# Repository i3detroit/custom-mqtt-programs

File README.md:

# I3Detroit custom esp IoT programs
This is where all the non-sonoff stuff that is simple lives

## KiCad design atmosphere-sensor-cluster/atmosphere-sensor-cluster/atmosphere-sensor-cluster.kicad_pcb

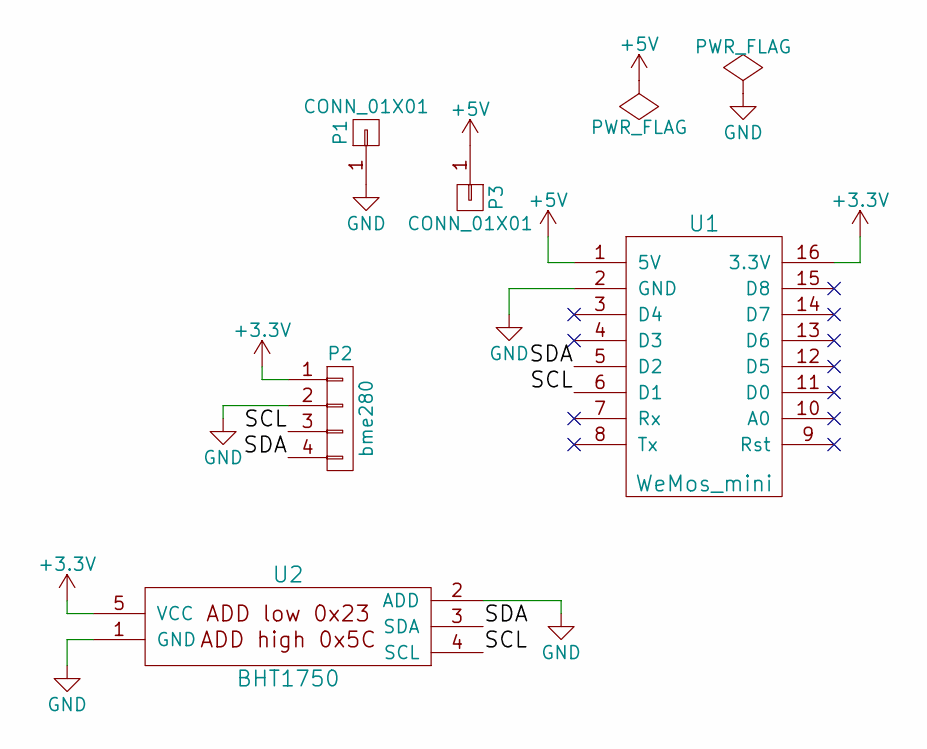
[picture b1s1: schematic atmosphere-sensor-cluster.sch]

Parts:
P1, P3: CONN_01X01; Pin_Header_Straight_1x01
P2: bme280; Pin_Header_Straight_1x04
U1: WeMos_mini; D1_mini_board
U2: BHT1750

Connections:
+3V3: P2.1, U1.16 (3.3V), U2.5 (VCC)
+5V: P3.1, U1.1 (5V)
/SCL: P2.3, U1.6 (D1), U2.4 (SCL)
/SDA: P2.4, U1.5 (D2), U2.3 (SDA)
GND: P1.1, P2.2, U1.2 (GND), U2.1 (GND), U2.2 (ADD)

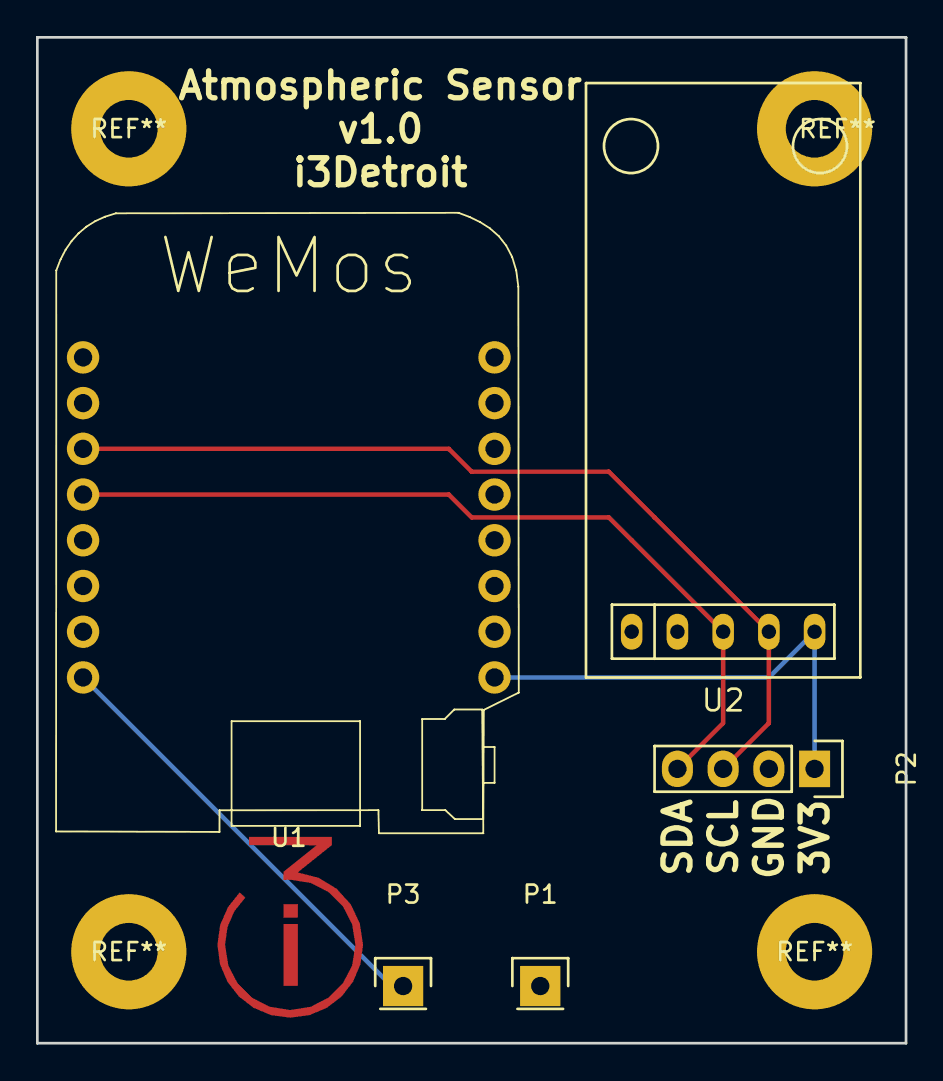
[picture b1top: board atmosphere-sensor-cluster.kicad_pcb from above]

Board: 2 copper layers, 48.3 x 55.9 mm, 6 parts (0 on the bottom side), 5 nets.

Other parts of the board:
i3Detroit: i3Logo1cm

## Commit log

2017-10-16 common; machine shop; bike zone switches
2017-10-28 Disco Ball buttons
2017-11-03 add machine-shop-motion-sensor
2017-11-03 Debounce machine shop motion sensor by 5 minutes
2017-11-04 Add air-compressor
2017-11-04 Add front-door-indicator and glass-door
2017-11-09 air compressor to infrastructure; debounce up a bit
2017-11-09 increase air compressor debounce
2017-11-09 Add 16seg
2017-11-09 16seg: Use mqtt-wrapper, move to iot vlan
2017-11-10 machine shop light switches: clean code; respond to poke
2017-11-14 rewire commons light switches
2017-11-14 air compressor publish status if set to current state
2017-11-14 fix names; return garage door state on query
2017-12-04 added publishing of off state
    now publishes ON for motion, and publishes OFF for no motion if motion isn't detected for a duration
2017-12-10 Made motion sensor generic
2017-12-10 machine shop light switches accept TOPIC/NAME
2017-12-10 disco generalized to single topic button; add led-matrix
2017-12-10 Front door indicator: Every minute read the i2c expander, hope this refreshes
2017-12-11 Add temperature clusters
2017-12-14 light 5 added to commons light switches; atmosphere snesor cluster bmp180 -> bmp280
2017-12-16 Update single topic button pins; query topic on start
2017-12-16 bike zone light switches -> middle east light switches
2017-12-17 Add light 10 back to commons light switches
2017-12-17 Single topic button -> multi topic button
2017-12-18 remove serial printing from multi-topic button
2017-12-20 multi-topic-button is now three topics
2017-12-20 glass door remove camel case; up debounce
2017-12-20 fix temperature sensor json
2017-12-20 update front door controller glass door topic subscription; fix new name in multi topic button
2017-12-20 add multi-topic-switch
2017-12-20 add attempt at updating front door controller, doesn't survive subscriptions
2017-12-20 add weather station, start fixing sparkfun bullshit
2017-12-22 Update front door panel, use funel
2017-12-25 sensor-cluster floatBuf wasn't big enough
    Probably causing the crashes we saw, and did fuck up the topic in a few
    cases.
2017-12-25 front door indicator tells when it pressed the shutdown button
2017-12-28 Move everything to new mqtt wrappper
2018-01-02 start on thermostat code, display is now functional
2018-01-06 Add light 25 to middle east light switches
2018-01-06 add inside to glass door topic
2018-01-06 commongs light switches pin change
2018-01-06 clasroom -> classroom
2018-01-06 commons lightswitch pin change again
    Why is it so broken.
2018-01-13 Thermostat looks like it works
2018-01-20 move display positioning to be centered
2018-01-20 ignore bin files
2018-01-20 laser status lights program
2018-01-20 blast gate monitor added
2018-01-23 renumbered, changed delay
2018-01-24 add thermostat eeprom to save state
2018-01-24 blast gate sensors working
2018-01-24 reportState fixed ouput
2018-01-26 atmosphere sensor cluster bmp280->bme280
2018-01-27 thermostat bmp280 -> bme280
2018-01-28 Add swing; fan control
2018-01-28 Update thermostat.ino
    Adjust display to US standards.
2018-01-30 Remove fan control while in auto mode
    Turns out the thermostat will do everything for you, the relay will just
    force the fan to be on.
2018-01-31 Add thermostat schematic, not finished
2018-01-31 device DEFINE, lightss only when laser on
2018-01-31 fixed laser topic to not fuck everything up
    nested topics = bad when devices subscribe to topic/#
2018-02-01 string macro expansion attempted but not working
2018-02-01 DEVICE needs to be quoted
2018-02-01 thermostat reads temp as float not int
    Oops.
    Now it swings both ways.
2018-02-03 switches identify on button press
2018-02-03 all buttons publish ID on press
2018-02-12 broken ftoa -> dtostrf in thermostat
    Also debug printing macros
2018-02-13 atmosphere sensor cluster ftoa -> dtostrf
2018-02-27 thermostat ftoa -> dtostrf
2018-03-14 Front door controller will now doorbell with no mqtt
2018-03-19 front door indicator doorbell hardware fixes
2018-03-20 16seg to new wrapper
2018-05-02 fix thermostat cooling logic
2018-05-27 added water cooler flow meter
2018-05-27 front door indicator publishes battery voltage
2018-05-27 front door indicator emergecy lights on button
2018-05-27 front door indicator tracks front door opened
2018-05-27 fix front door indicator garage LEDs
2018-06-09 Thermostat forces fan on for cold.
2018-06-16 added front door query functionality
2018-06-16 fixed garage and front door button_state indices garage door was reporting shutdown button state when queried
2018-06-23 fixed null topic, changed states to lower case, fixed whitespace in json
2018-07-03 multi-topic switch has telemetry for the topics
2018-08-07 readTemp always dirty
2018-08-07 State structs; publish stat/tele better
2018-08-07 Thermostat V2 board/code; atmosphere sensor board/code; kicad libs
    thermostat uses mcp23017, also fixed cooling logic?
    Commit d1_mini_kicad library sumodule as files instead of sumodule
    git@github.com:jerome-labidurie/d1_mini_kicad.git
    update thermostat kicad stuff for new libs
    thermostat: finish schematic and start layout
    Layout progress
2018-08-07 Save timeout interval to eeprom
2018-08-07 TODOS for mqtt interface
2018-08-07 Thermostat displays connected state
2018-08-07 untested: might delay fan after turning on furnace/aircon
2018-08-07 Rewrite fan delay; split doControl into file; start ateempt at tests
2018-08-07 actually initialize bool of if we have a temp sensor
2018-08-07 fan logic works; eeprom broken
2018-08-07 thermostat testing code define not set by platformio
2018-08-07 front door indicator to mcp23017; remove front door funnel
2018-08-08 Front door indicator battery voltage publish 10s->60s
2018-08-20 added reporting of input (target, requested mode, etc) reports on change and with regular telemetry
2018-08-21 fixed target reporting after automatic reset
2018-08-21 added laser-cut thermostat case plans
2018-09-03 non-working mqtt timeout command
2018-09-03 cleanup command parsing; broken magic in timeout
2018-09-03 thermostat timeout works; all commands take null to print current
2018-09-03 Thermostat test attempt
2018-09-03 fan delay to 30 seconds
2018-09-03 thermostat clean up callback; swing can't be 0 fixed
2018-09-03 track if thermostat has power from mains or battery
2018-09-03 report state cleanup
2018-09-03 thermostat Cleanup reset; mqtt interface cleanup
2018-09-03 cleanup merge conflict issue, change sensor pub topic to sensors
2018-09-03 themostat rename sensor field
2018-09-03 thermostat: always publish input with status interval
2018-09-04 eeprom setup cleanup
2018-09-14 motion sensor logic was inverted
2018-09-17 thermostat query command
2018-10-08 fixed typo
2018-10-08 first pass, maybe works?
2018-10-09 fixed and functional
2018-10-11 Thermostat Testing patch from Kevin
2018-10-15 code actually works now, still needs cleanup
2018-10-15 updated, but still wrong
2018-10-15 cleanup
2018-10-15 fixed relay wiring
2018-10-17 never start opening if limit switch is pressed
2019-01-13 adding sign character limit handling
2019-03-24 thermostat: battery icon; don't show temp if OFF
2019-07-10 setting up project with platformio
2019-07-10 remove unnecessary build flags fuckery
2019-07-19 remove before adding submodules
2019-07-19 add libraries as submodules
2019-07-26 remove printing battery status while it's broken
2019-07-26 library updates and fixes
2019-07-26 renamed for platfromio compatibility
2019-10-08 Thermostat checks mqtt inputs better
    no atoi, checks strtol/strtoul properly.
2019-11-12 add laser timer to repo
2020-01-20 fix(platformio.ini): don't use espressif8266@1.5.0 cause it breaks stuff
2020-01-23 fix(thermostat): accept target commands with fractional components
    target 19.0, for example which is what hass sends
2020-02-15 fix(thermostat)!: change output state words to match hass
    heat -> heating;
    cool -> cooling
2021-01-18 remove lib dir
2021-01-23 split atmosphere sensor out into its own repo
